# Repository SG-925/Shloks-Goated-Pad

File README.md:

Overview:
Shlok's Goated pad is a macropad that I will use for CAD. Currently all of the keys are mapped to functions that I will use. It has 9 keys, 2 LEDs and uses Kmk filmware.

Cad:
Only case:

Case With PCB:

Fully assembled

Schematic:

PCB:

BOM:
- Seeed XIAO RP2040 x1
- Cherry MX switches x9
- PCB x1
- Blank DSA keycaps x9
- M4x16mm screws x4
- 2× SK6812 MINI-E addressable RGB LEDs

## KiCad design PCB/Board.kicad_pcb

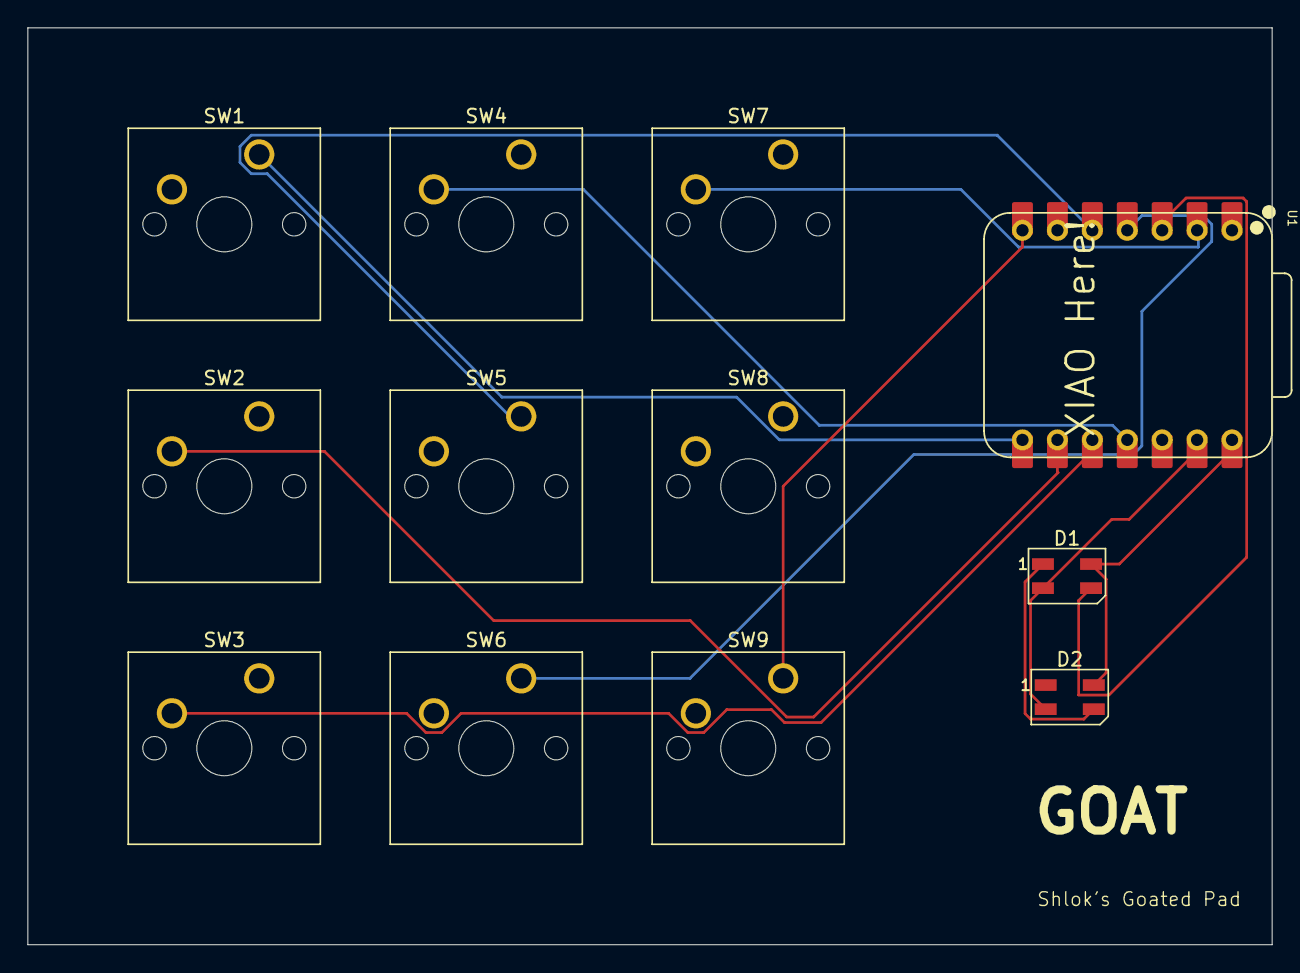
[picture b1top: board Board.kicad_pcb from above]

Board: 2 copper layers, 90.5 x 66.7 mm, 12 parts (0 on the bottom side), 9 nets.

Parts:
D1, D2: SK6812MINI; LED_SK6812MINI_PLCC4_3.5x3.5mm_P1.75mm
SW1, SW2, SW3, SW4, SW5, SW6, SW7, SW8, SW9: SW_Push; SW_Cherry_MX_1.00u_PCB
U1: XIAO-RP2040-DIP

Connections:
+5V: D1.4 (VDD), D2.4 (VDD), U1.14 (VBUS)
GND: D1.2 (VSS), D2.2 (VSS), SW1.2, SW2.1, SW3.1, SW4.1, SW5.2, SW6.2, SW8.2, SW9.2, U1.13 (GND)
unnamed: D1.3 (DIN), U1.3 (GPIO28/ADC2/A2)
unnamed: D1.1 (DOUT), D2.3 (DIN)
unnamed: SW1.1, SW2.2, SW3.2, SW4.2, SW9.1, U1.7 (GPIO0/TX), U1.8 (GPIO1/RX), U1.9 (GPIO2/SCK), U1.10 (GPIO4/MISO), U1.11 (GPIO3/MOSI)
unnamed: SW5.1, U1.5 (GPIO6/SDA)
unnamed: SW8.1, U1.1 (GPIO26/ADC0/A0)
unnamed: SW7.2, U1.2 (GPIO27/ADC1/A1)
unnamed: SW6.1, U1.4 (GPIO29/ADC3/A3)

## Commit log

2026-01-01 Add Scheme
2026-01-01 add project file
2026-01-01 Add board
2026-01-01 add python code
2026-01-01 Rename Board to Board.kicad_pcb
2026-01-01 Rename Project to Project.kicad_pro
2026-01-01 Rename scheme to scheme.kicad_sch
2026-01-01 Enhance README with schematic, PCB, and BOM details
    Added detailed sections for schematic, PCB, and BOM.
2026-01-02 Update PCB schematic with junctions and power symbol
    Added multiple junctions and wires to the schematic, modified switch positions, and replaced a switch with a power symbol for ground.
2026-01-05 Update README with additional images
    Added images for the case with PCB and fully assembled macropad.
2026-01-05 Update print statement from 'Hello' to 'Goodbye'
2026-01-05 Create Full Assembly
2026-01-05 Add SK6812 MINI-E RGB LEDs to parts list
2026-01-07 Add labels and clean up PCB segments
    Added text labels to the PCB design for better identification and removed several unnecessary segments.
